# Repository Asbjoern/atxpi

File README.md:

# atxpi #

Raspberry Pi ATX power controller using the [teensy](http://www.pjrc.com/teensy/) microcontroller. The atxpi emulates ACPI behavior, handling ATX power supply states, power / reset buttons, and LEDs.

---

 - [Parts List](#parts-list)
 - [Power / Reset Buttons](#buttons)
 - [GPIO Pins](#gpio)
 - [RPI Power Scripts Installation](#power-scripts)
	- [Arch](#power-scripts-arch)
	- [Raspbian](#power-scripts-raspbian)
 - [Schematic](#schematic)

---

<h2 id="parts-list">Parts List</h2>

 - [Teensy 2.0](http://www.pjrc.com/store/teensy.html)
 - [Logic Level Converter](https://www.sparkfun.com/products/11978)
 - [ATX Connector Breakout Board](https://www.sparkfun.com/products/9558)
 - [ATX Power Supply Connector](https://www.sparkfun.com/products/9498)

---

<h2 id="buttons">Power / Reset Buttons</h2>

 - Power state 0:
	- Power button pressed: power on
	- Reset button pressed: do nothing

 - Power state 1:
	- Power button pressed for 1 second: Tell RPI to shutdown by setting GPIO pin 23 HIGH
	- Power button pressed for 5 seconds: Force power off
	- Reset button pressed for 1 second: Force power cycle

---

<h2 id="gpio">GPIO Pins</h2>

The RPI will monitor GPIO 23 and shutdown if it is set to HIGH. After the RPI boots it will set GPIO 24 HIGH, telling the teensy that the RPI is up. When GPIO 24 goes from HIGH to LOW the teensy will wait 5 seconds then cut power, unless GPIO 25 is HIGH. GPIO 25 is set to HIGH when the RPI is rebooting, preventing the teensy from cutting power when GPIO 24 changes from HIGH to LOW.

---

<h2 id="power-scripts">RPI Power Scripts Installation</h2>

<h3 id="power-scripts-arch">Arch</h3>

Log into the RPI and become root. You will need to install git and WiringPi:

	[root@alarmpi ~]$ pacman -Sy git wiringpi

Next, clone the repo and copy required files.

	[root@alarmpi ~]$ git clone https://github.com/steelcaverobotics/atxpi.git
	[root@alarmpi ~]$ mkdir /opt/atxpi
	[root@alarmpi ~]$ cp atxpi/rpi_power_scripts/*.sh /opt/atxpi/
	[root@alarmpi ~]$ chmod 755 /opt/atxpi/*.sh
	[root@alarmpi ~]$ cp atxpi/service_files/arch/*.service /usr/lib/systemd/system/

Then enable the services, skipping `atxpi-gpio-shutdown.service` if you don't want the RPI to shutdown when the power button is pressed.

	[root@alarmpi ~]$ systemctl enable atxpi-gpio-boot.service
	[root@alarmpi ~]$ systemctl enable atxpi-gpio-reboot.service
	[root@alarmpi ~]$ systemctl enable atxpi-gpio-shutdown.service

Finally, start the services. Do not start `atxpi-gpio-reboot.service`, as this will be started when the RPI is rebooting.

	[root@alarmpi ~]$ systemctl start atxpi-gpio-boot.service
	[root@alarmpi ~]$ systemctl start atxpi-gpio-shutdown.service

<h3 id="power-scripts-raspbian">Raspbian</h3>

Log into the RPI and become root. You will need to install git and WiringPi:

	root@raspberrypi:~# apt-get install git-core
	root@raspberrypi:~# git clone git://git.drogon.net/wiringPi
	root@raspberrypi:~# cd wiringPi/
	root@raspberrypi:~# ./build

Next, clone the repo and copy required files.

	root@raspberrypi:~# git clone https://github.com/steelcaverobotics/atxpi.git
	root@raspberrypi:~# mkdir /opt/atxpi
	root@raspberrypi:~# cp atxpi/rpi_power_scripts/*.sh /opt/atxpi/
	root@raspberrypi:~# chmod 755 /opt/atxpi/*.sh
	root@raspberrypi:~# cp atxpi/service_files/raspbian/* /etc/init.d/
	root@raspberrypi:~# chmod 755 /etc/init.d/atxpi-gpio-*

Then enable the services, skipping `atxpi-gpio-shutdown` if you don't want the RPI to shutdown when the power button is pressed.

	root@raspberrypi:~# update-rc.d atxpi-gpio-boot defaults
	root@raspberrypi:~# update-rc.d atxpi-gpio-reboot defaults
	root@raspberrypi:~# update-rc.d atxpi-gpio-shutdown defaults

Finally, start the services.

	root@raspberrypi:~# /etc/init.d/atxpi-gpio-boot start
	root@raspberrypi:~# /etc/init.d/atxpi-gpio-shutdown start

---

<h2 id="schematic">Schematic</h2>

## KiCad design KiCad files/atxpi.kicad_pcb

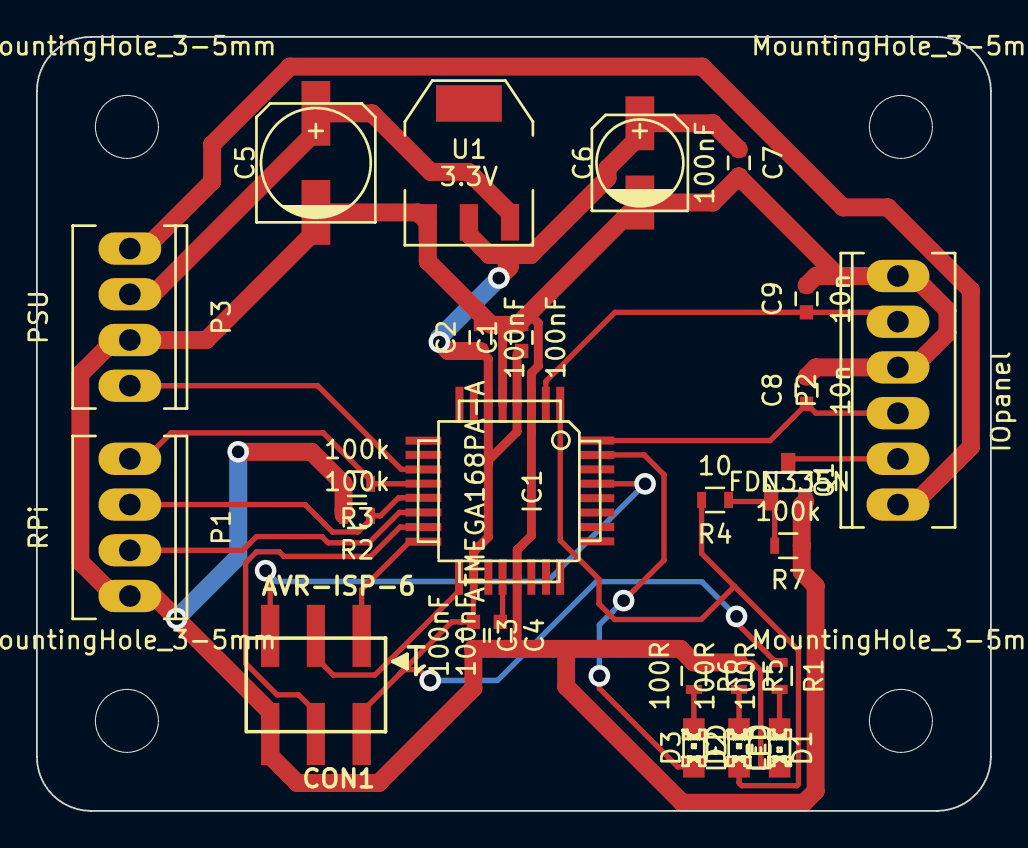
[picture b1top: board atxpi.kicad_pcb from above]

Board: 2 copper layers, 53.0 x 43.0 mm, 30 parts (0 on the bottom side), 22 nets.

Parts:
C1, C2, C3, C4, C7: 100nF; C_0603
C5: >100uF; c_elec_6.3x5.8
C6: 10uF; c_elec_5x5.3
C8, C9: 10n; C_0603
CON1: AVR-ISP-6; pin_2x6_smd
D1, D2, D3: LED; LED-0805
IC1: ATMEGA168PA-A; TQFP-32
MountingHole_3-5mm, MountingHole_3-5mm#2, MountingHole_3-5mm#3, MountingHole_3-5mm#4: VAL**; MountingHole_3-5mm
P1: RPi; Socket_MOLEX-KK-RM2-54mm_Lock_4pin_straight
P2: IOpanel; Socket_MOLEX-KK-RM2-54mm_Lock_6pin_straight
P3: PSU; Socket_MOLEX-KK-RM2-54mm_Lock_4pin_straight
Q1: FDN335N; SOT-23
R1, R5, R6: 100R; R_0603
R2, R3, R7: 100k; R_0603
R4: 10; R_0603
U1: 3.3V; SOT-223

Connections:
+3.3V: C1.1, C2.1, C3.1, C6.1, C7.1, CON1.2, IC1.4, IC1.6, IC1.18, R1.1, U1.2
+5V: C5.1, P3.2, U1.3
+12V: P2.1, P3.1
/MISO: CON1.1, IC1.16
/MOSI: CON1.4, IC1.15
/PS_ON: IC1.11, P3.4
/PWR_LED: D2.1, IC1.1, R4.2
/PWR_SW: C8.1, IC1.32, P2.3
/RDY_LED: D3.1, IC1.31
/RPI_REBOOT_25: IC1.12, P1.1, R3.1
/RPI_UP_24: IC1.13, P1.2, R2.1
/RST: CON1.5, IC1.29
/RST_SW: C9.1, IC1.2, P2.5
/SCK: CON1.3, IC1.17
/SHTDWN_23: IC1.14, P1.3
GND: C1.2, C2.2, C3.2, C4.2, C5.2, C6.2, C7.2, C8.2, C9.2, CON1.6, D1.2, IC1.3, IC1.5, IC1.21, P1.4, P2.4, P2.6, P3.3, Q1.2, R2.2, R3.2, R5.1, R6.1, R7.1, U1.1
unnamed: C4.1, IC1.20
unnamed: D1.1, R1.2
unnamed: D2.2, R5.2
unnamed: D3.2, R6.2
unnamed: P2.2, Q1.3
unnamed: Q1.1, R4.1, R7.2

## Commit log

2013-09-16 started atxpi code for the teensy2.0 microcontroller
2013-09-16 changed file type
2013-09-18 implemented power and reset button functionality
2013-09-24 implemented rpi gpio functionality and added debugging
2013-09-27 turned off debug, added hdd led, and changed pin numbers
2013-09-28 changed forced shutdown and reset times
2013-11-11 add atxpi eagle schematic
2013-11-11 update and fix atxpi schematic
2013-11-27 add atxpi schematic png
2013-11-27 add rpi power scripts
2013-11-27 fix gpio pin number in reboot.sh
2013-11-28 add serial debug control
2013-11-28 add arch service files and update README.md
2013-11-28 add raspbian init scripts and update README.md
2014-02-11 add atxpi board
2014-03-21 GPLv3
2015-05-08 Replaced Teensy/Eagle hardware with ATMEGA328 PCB mounted design
2015-05-08 Swithed pins to new design and replaced Bounce with Bounce2 library
